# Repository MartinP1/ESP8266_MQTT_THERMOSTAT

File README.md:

# Ein Heizkörperthermostat auf Basis eines ESP8266 und MQTT

## Projektstand
Das Projekt ist seit mehreren Jahren im operativen Einsatz.
- Temperaturmessung über 3 Sensoren, Weitergabe der Werte über MQTT
- Zuspielen der Solltemperatur über MQTT auf den ESP
- Ansteuerung von Lüftern, die den Heizkörper von unten zur Erhöhung der Heizleistung anblasen (PWM)
- Zeitplan für Änderung der Solltemperatur (realisiert über ein ioBroker Blockly Skript)
- Preferences library für Gerätekonfiguration über MQTT (kein hartverdrahteter Device Name im Quellcode mehr!)
- Fensterkontakt 
- OTA Library für den OTA-Update der Firmware

## Hardwareübersicht

- ESP basierte Hardware - es werden drei Module unterstützt.
  - D1 Mini (ESP8266) Probleme mit instabiler Spannungsversorgung (Arduino IDE "D1 Mini")
  - D1 Mini (ESP32 - seit 1.12.2023 - Arduino IDE "WEMOS D1 MINI ESP32")
  - S2 Mini (ESP32 - seit 1.12.2023 ) Neue Empfehlung!

- 12 V DC Spannungsversorgung - Ein Tisch-Netzteil von der Resterampe von [www.pollin.de](https://www.pollin.de/p/tischnetzteil-gp-1223c-12-v-2-3-a-5-5-2-1-mm-gebraucht-352200) 12V / 2,3A. 
- Danfoss Stellantrieb Thermot 230 V AC, M30x1,5 NC stromlos geschlossen [088H3220](https://store.danfoss.com/de/de/Climate-Solutions-W%C3%A4rmetechnik/Warmwasser-Fu%C3%9Fbodenheizungen/Thermische-Stellantriebe/Thermischer-Stellantrieb%2C-Thermot%2C-M-30-x-1-5%2C-Versorgungsspannung-%5BV%5D-%5BAC%5D%3A-230%2C-NC-%28stromlos-geschlossen%29%2C-1-00-m/p/088H3220) ca 10 €
  - angesteuert über ein Kleinrelais
- 4 Arctic 80 mm Gehäuselüfter ([3 Pin](https://www.arctic.de/F8/ACFAN00205A) habe ich gekauft, wahrscheinlich wäre [4 Pin](https://www.arctic.de/P8-PWM/ACFAN00149A) die bessere Wahl gewesen) blasen den Heizkörper von unten an
- 3 DS 18B20 Thermosensoren von Shelly https://www.pollin.de/p/shelly-temperMQTT_PUB_DEV_PREFIXatursensor-ds18b20-591021
  - zur Messung von Zulauf- und Ablauftemperatur des Heizkörpers und der Raumtemperatur

Das Prototyp-System ist stillgelegt, aktuell läuft V1 einer Kicad-Leiterplatte.
Mindestausstattung wäre ein Thermosensor für die Raumtemperatur und ein Schaltrelais für die Ansteuerung des Ventil-Stellgliedes...

## Unsortiertes

### Lüfter-Aufrüstung

Inzwischen laufen acht 80 mm Lüfter unter dem Heizkörper - Blasen in die Lücke zwischen den Platten
Dazu noch 6 50 mm Lüfter, die in die Zwischenraum zwischen der Wand und dem Heizkörper blasen

Stromaufnahme ca 1,2 A, 11,1 V
PWM-Frequenz 8 kHz
Die hinzugekommenen 80mm Lüfter sind BLDC Typen. Laufen nicht unter PWM -> Glätten ist angesagt..

Ein simpler 220 uF Elko schafft das. Wird aber heiß da fehlt wohl noch eine Induktivität, um die Stromspitzen vom Eko fernzuhalten...

Rechnung 

1,2A/8000 Hz = 0,00015 As
Spannungeinbruch um 7 V (Auf 5 V) 

0,00015 As / 7 V = 22 &mu;F

220 &mu;F passt schon

Induktivität 2 A Max Vs/A - 220 &mu;H????

Schaltung aufgebaut, funktioniert.
Glättet das Signal ziemlich gut, Lüfter  laufen alle, aber die Spannungen sind deutlich geringer, als ohne Induktivität

Elektrolytkondensator 220 &mu;F, (Grabbelkiste) 
Induktivität 330 &mu;H Von Amazon
> sourcing map 5 Stück Ringkern Induktivität Kupferspule magnetische Induktivität 330uH 5A für DIY Platine

Messung: Full-Power Strom 1,16 A

| PWM | Spannung | Bemerkung |
| - | - | - |
| 255 | 10.9 V | Laut |
| 250 | 9.6 V | |
| 240 | 9.2 V | Hörbar |
| 220 | 8.3 V | |
| 200 | 7.2 V | Leise |
| 180 | 6.5 V | |
| 165 | 5.7 V | Unhörbar |
| 150 | 5.1 V | |
| Darunter | x | Verschiedene Lüfter stehen still |

### Was fehlt noch

- Schaltplanänderung in Kicad nachpflegen, zur Stabilitätsverbesserung werden die DS18B20 jetzt mit 5 V versorgt

### Verbesserungen - was würde ich in der Serie anders machen

- 4 Pin Lüfter?
- 24 V Variante des Danfoss Stellantriebs über DCDC Wandler mit Enable-Eingang?
- Full Fan speed konfigurierbar (255 scheint zu schnell zu sein ...)
- Neues Leiterplattenlayout mit 230 V Spannungsversorgung und <del>Schaltrelais</del> Solid State Relay (für PWM) für Danfoss-Stellglied
- Migration des Projekts von Arduino-IDE auf PlatformIO

### Worklog

- JAN-2024 Start der Nutzung der Preferences Bibliothek
- MAR-2025 Diverse Code-Korrekturen bzgl. der Temperatursensoren.
- SEP-2025 
  - ASYNC_TCP issues fixed use AsyncTCP by ESP32Async 3.4.7 
  - OTA Update librariy added 
- OCT-2025             
  - Moved to espMqttClient https://github.com/bertmelis/espMqttClient/blob/main/src/espMqttClient.h
    - that fixed stability problems on esp32 single core chips
- FEB-2026 
  - changed behaviour on desired throttle speed (1.2.5)
  - p-controller on room temp diff between -hyst and 0 (1.2.6)
  - 
## Bugs 

- serial logging does not work reliable any more since 1.2.6 -> fixed by updating ESP32 board lib from 3.3.5 to 3.3.6

## Unklarheiten

Wenn man den Client an einen Mosquitto anschließt, und beim Schreiben des Mosquittos 
immer den Wert "Echoed" passieren komische Sachen. Beim MQTT-Adapter des ioBroker nicht ...

Wenn nach der Verbindungsaufnahme mit dem Broker vom Broker eine Null für den Wert kommt, 
ein Publish mit den "Werkseinstellungen" machen?

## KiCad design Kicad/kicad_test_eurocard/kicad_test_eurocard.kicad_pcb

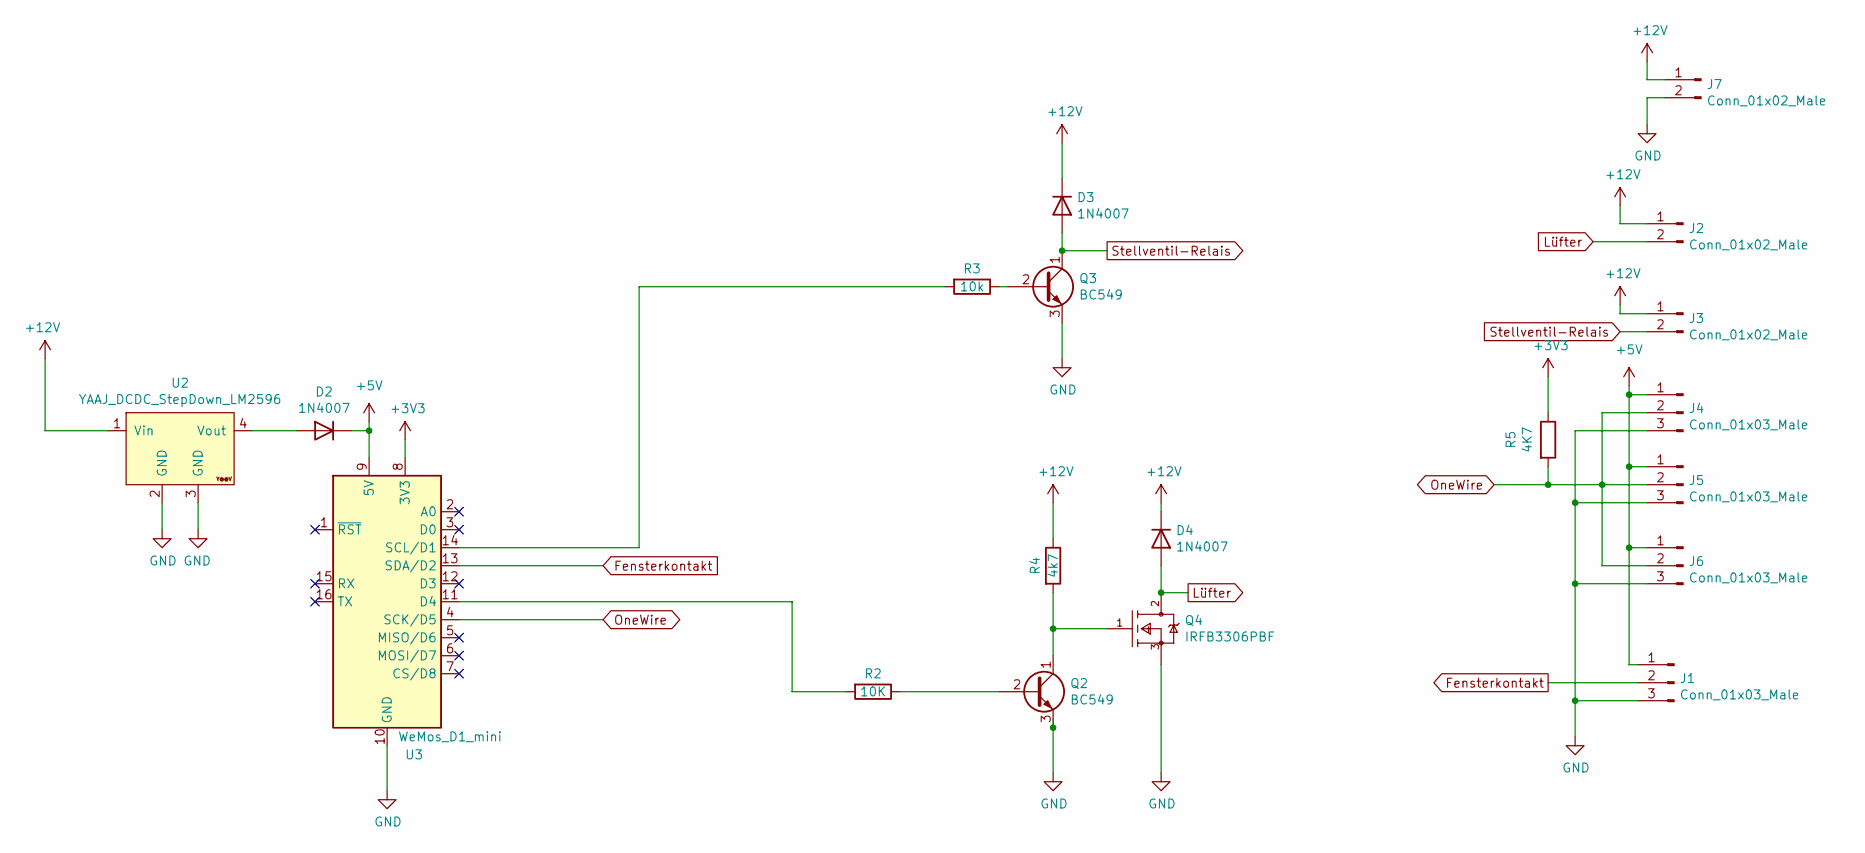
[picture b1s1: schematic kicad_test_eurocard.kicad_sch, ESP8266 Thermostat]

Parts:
D2, D3, D4: 1N4007; D_DO-41_SOD81_P10.16mm_Horizontal
J1, J4, J5, J6: Conn_01x03_Male; PinHeader_1x03_P2.54mm_Vertical
J2, J3, J7: Conn_01x02_Male; PinHeader_1x02_P2.54mm_Vertical
Q2, Q3: BC549; TO-92_Inline
Q4: IRFB3306PBF; Infineon_Technologies-PG-TO220-3-02_2008-904-MFG; mouser part number 942-IRFB3306PBF; digikey description MOSFET N-CH 60V 120A TO-220AB
R2: 10K; R_Axial_DIN0207_L6.3mm_D2.5mm_P10.16mm_Horizontal
R3: 10k; R_Axial_DIN0207_L6.3mm_D2.5mm_P10.16mm_Horizontal
R4: 4k7; R_Axial_DIN0207_L6.3mm_D2.5mm_P10.16mm_Horizontal
R5: 4K7; R_Axial_DIN0207_L6.3mm_D2.5mm_P10.16mm_Horizontal
U2: YAAJ_DCDC_StepDown_LM2596
U3: WeMos_D1_mini; WEMOS_D1_mini_light

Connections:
+3V3: R5.1, U3.8 (3V3)
+5V: D2.1 (K), J1.1, J4.1, J5.1, J6.1, U3.9 (5V)
+12V: D3.1 (K), D4.1 (K), J2.1, J3.1, J7.1, R4.1, U2.1 (Vin)
Fensterkontakt: J1.2, U3.13 (SDA/D2)
GND: J1.3, J4.3, J5.3, J6.3, J7.2, Q2.3 (E), Q3.3 (E), Q4.3 (S), U2.2 (GND), U2.3 (GND), U3.10 (GND)
Lüfter: D4.2 (A), J2.2, Q4.2 (D)
unnamed: D2.2 (A), U2.4 (Vout)
unnamed: Q2.2 (B), R2.1
unnamed: Q2.1 (C), Q4.1 (G), R4.2
unnamed: Q3.2 (B), R3.1
unnamed: R2.2, U3.11 (D4)
unnamed: R3.2, U3.14 (SCL/D1)
OneWire: J4.2, J5.2, J6.2, R5.2, U3.4 (SCK/D5)
Stellventil-Relais: D3.2 (A), J3.2, Q3.1 (C)

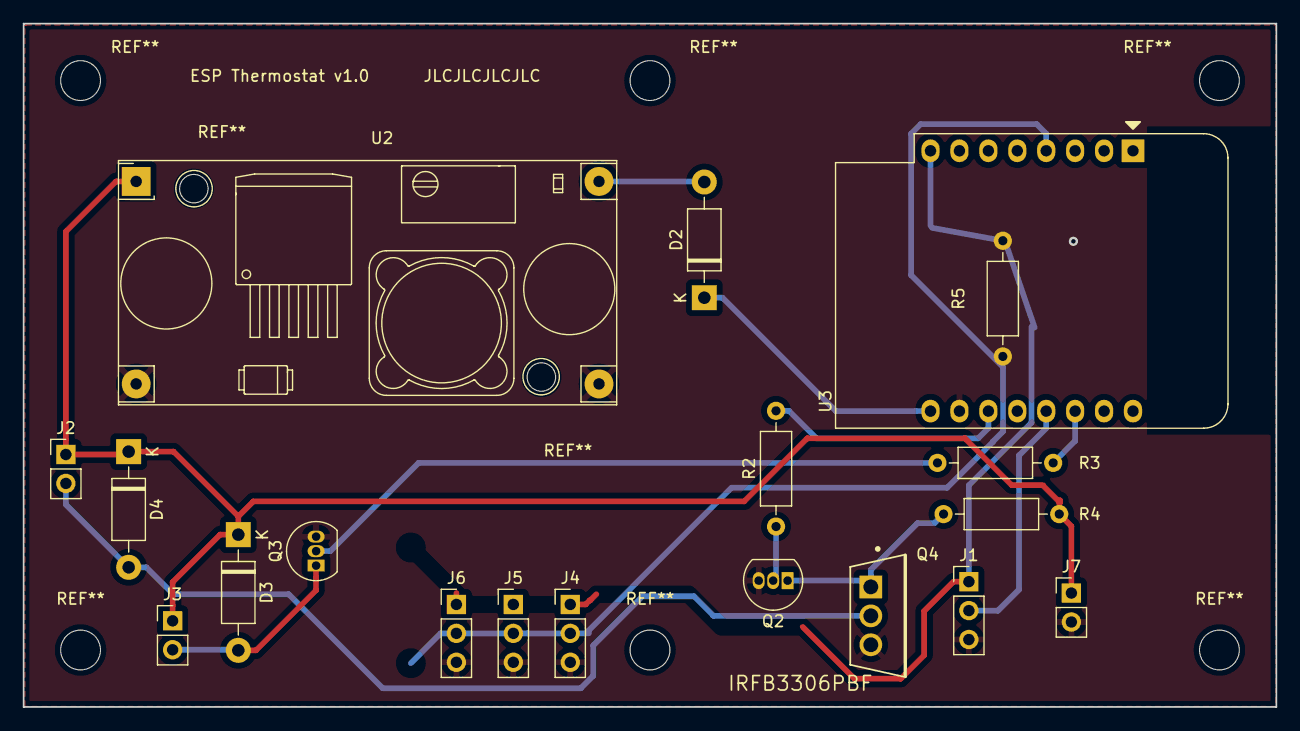
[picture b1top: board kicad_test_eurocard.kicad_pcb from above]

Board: 2 copper layers, 110.0 x 60.0 mm, 19 parts (0 on the bottom side), 14 nets.

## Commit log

2023-02-28 initial
2023-02-28 gitignore
2023-02-28 pwm eingebaut
2023-02-28 Schaltplan
2023-03-02 Sketch in mehrere Files aufgebrochen, sollte so ggfs beim Editieren überschaubarer sein...
2023-03-02 more splitting of source files
2023-03-03 logging improved
2023-03-09 minor changes with notebook
2023-03-11 regler angefangen und kicad
2023-03-11 neues file
2023-03-11 zwischenstand
2023-03-12 erster livetest
2023-03-12 beta-lauffaehig
2023-03-12 readme angepasst
2023-03-13 calc changed
2023-03-16 fan throttle hysteresis
2023-03-16 fan throttle linear regulation
2023-03-17 Feinschliff Hysterese
2023-03-18 Fanspeed automat
2023-03-19 Fanspeed automat 2
2023-03-19 Fanspeed automat 3
2023-03-20 hysterese 3
2023-03-20 MQTTLogging
2023-03-21 logging
2023-03-22 logging expanded
2023-03-24 logging printf
2023-05-23 Kicad Schematics
2023-08-12 Async wifi changed
2023-09-22 delay after publish
    smoothen Wlan traffic peaks
2023-09-24 Update MQTT_DS18B20.ino
    Desired nodes not longer published
2023-11-30 ESP32 + VSCode
    ESP32 Anpassungen und Wechsel auf VSCode
2023-12-01 D1 MINI, D1_MINI32 and S2_MINI supported
    Adaptations for three different boards now
2023-12-04 Board Type defines revised
    Board type logging in build process
2023-12-05 other board
2024-01-07 conf in flash
    Begin Configuration in flash memory work
2024-01-21 Preferences Lib support
    Begin work
2024-01-21 Prefecences lib
2024-05-20 Defines for index
2024-05-20 Kaputt
    Kaputt!
2024-05-20 Update c_cpp_properties.json
    Handkorrekturen!
2024-05-20 Build works again!
    With Arduino IDE
2024-06-09 Preferences MqttName
    Added preferences library preserved configureable MqttName
2024-06-12 fixed preferences and pwm
2024-06-13 c&p code snippets removed
    Editor seems to be crappy ...
2024-06-13 corrupted ino file fixed
    Sleep mode Linux PC not working?
2024-06-13 PWM
    PWM Testing (not working at all)
2024-06-13 selftest debug
2024-06-13 Debug first version
2024-06-15 gitignore
    added c_cpp_properties.json to gitignore
2024-06-16 thermostat_preferences.h added
    preferences treatment in separate file
2024-06-16 Prefs, mqtt
    Preferences code refactored, echoing MQTT messages added.
    Mqtt reconnect on MQTT disconnect added
2024-06-16 Update MQTT_DS18B20.ino
    MQTT Reconnect
2024-06-16 Update README.md
    Tippfehler, Ergänzungen
2024-06-17 wifi mqtt reconnect
    wifi and mqtt reconnect moved from timer to loop()
2024-06-17 wifiStatus
    Avoid regulary work if wifi and mqtt is not up and running (test purpose)
2024-06-18 no ticker lib
    ticker lib removed
    standalone functionality restored
2024-06-19 Mesh scan for best AP
2024-07-17 no publish on mqtt down
2024-07-19 arduino.json
2024-07-19 MQTT Fix
    Wifi RSSI report to MQTT fixed
2024-10-11 fehltemperaturfilter
2025-02-05 Update README.md
    nur zum Test
2025-03-08 ino renamed
2025-03-09 Download code options
    Load binary to chip from a drifferent server beside Desktop PC, to avoid wired USB connection to Desktop PC
2025-03-09 bash scripts renamed
2025-03-09 flash_S2.sh
2025-03-09 remote programming scripts updated
    intermediate not working state
2025-03-09 Scripts are working
2025-03-09 Kicad included
2025-03-10 upload binary script
    * invisible password entry
    * selector for binary subdir improved
2025-03-11 intermediat not working state
2025-03-11 DS18B20 diagnostics added
    Hopefully provides hints whether onewire library is defiective or one of the sensor is faulty...
2025-03-12 Recovery Thermosensor MQTT Logging
2025-03-13 english readme and temperature logging
2025-03-13 readme improved
2025-03-16 sensorstatus
    Sensorstatus
2025-03-16 preisliste
2025-05-09 sensor scanning improved
2025-05-12 worklog
2025-05-12 worklog2
2025-09-15 asynctcp library updated
2025-09-16 Pullup
2025-09-28 OTA added
2025-09-28 Readme
2025-09-29 Fensterkontakt beginn
2025-09-29 Window Contact 2
2025-09-29 window contact refined
2025-09-30 Readme und Stability
2025-09-30 Startup errors evaluated
2025-09-30 More changes, but no better startup stability
2025-10-01 Serial.begin is necessary, logging added
2025-10-02 Wakeup problems fixed
    connectToWifi in too short sequence between setup() and loop()
2025-10-03 Zwischenstand!
    Window Sensor MQTT and startup stability experiments.
2025-10-06 changed MQTT Lib ewpMqttClient by bertmelis
2025-10-06 Cleanup and adaptations
2026-02-01 Bugfix
2026-02-02 Luefter
2026-02-02 Update README.md
    Changed Todo
2026-02-05 Fan-Steuerung mit P-Regler
2026-02-05 Administrative Work for 1.2.6 Version
2026-02-05 layout of release log
2026-02-05 Gnuplot PWM vs Voltage
2026-02-05 kurve
2026-02-05 program on debian test
2026-03-13 delay added after requestTemperatures
